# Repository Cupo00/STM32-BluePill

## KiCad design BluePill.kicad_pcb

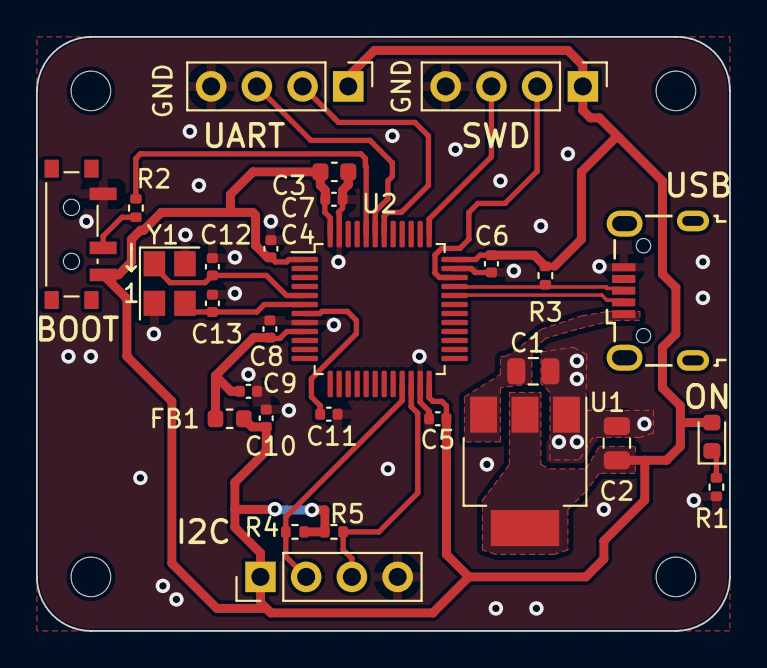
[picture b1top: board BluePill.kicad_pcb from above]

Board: 2 copper layers, 38.5 x 33.0 mm, 32 parts (0 on the bottom side), 18 nets.

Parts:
C1, C2: 22u; C_0805_2012Metric
C3: 10u; C_0603_1608Metric
C4, C5, C6, C7, C11: 100n; C_0402_1005Metric
C8: 10n; C_0402_1005Metric
C9, C10: 1u; C_0402_1005Metric
C12, C13: 10pF; C_0402_1005Metric
D1: LED; LED_0603_1608Metric
FB1: 120R; L_0603_1608Metric
H4, H4#2, H4#3, H4#4: MountingHole; MountingHole_2.2mm_M2
J1, J2, J3: Conn_01x04_Male; PinHeader_1x04_P2.54mm_Vertical
J4: USB_B_Micro; USB_Micro-B_Wuerth_629105150521
R1, R3, R4, R5: 1k5; R_0402_1005Metric
R2: 10k; R_0402_1005Metric
SW1: SW_SPDT; SW_SPDT_PCM12
U1: AMS1117-3.3; SOT-223-3_TabPin2
U2: STM32F103C8T6; LQFP-48_7x7mm_P0.5mm
Y1: 16MHz; Crystal_SMD_3225-4Pin_3.2x2.5mm

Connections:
+3.3V: C2.1, C3.1, C4.1, C5.1, C6.1, C7.2, C10.1, D1.2 (A), FB1.2, J1.1, J2.1, J3.1, R3.1, R4.1, R5.1, SW1.3 (C), U1.2 (VO), U2.1 (VBAT), U2.24 (VDD), U2.36 (VDD), U2.48 (VDD)
+3.3VA: C8.1, C9.1, FB1.1, U2.9 (VDDA)
/HSE_In: C12.1, U2.5 (PD0), Y1.1
/HSE_Out: C13.1, U2.6 (PD1), Y1.3
/I2C2_SCL: J2.2, R4.2, U2.21 (PB10)
/I2C2_SDA: J2.3, R5.2, U2.22 (PB11)
/NRST: C11.1, U2.7 (NRST)
/PWR_LED_K: D1.1 (K), R1.1
/SWCLCK: J3.3, U2.37 (PA14)
/SWDIO: J3.2, U2.34 (PA13)
/USART1_RX: J1.3, U2.43 (PB7)
/USART1_TX: J1.2, U2.42 (PB6)
/USB_D+: J4.3 (D+), R3.2, U2.33 (PA12)
/USB_D-: J4.2 (D-), U2.32 (PA11)
/sw_boot0: R2.1, SW1.2 (B)
GND: C1.2, C2.2, C3.2, C4.2, C5.2, C6.2, C7.1, C8.2, C9.2, C10.2, C11.2, C12.2, C13.2, J1.4, J2.4, J3.4, J4.5 (GND), R1.2, SW1.1 (A), U1.1 (GND), U2.8 (VSSA), U2.23 (VSS), U2.35 (VSS), U2.47 (VSS), Y1.2, Y1.4
unnamed: R2.2, U2.44 (BOOT0)
VBUS: C1.1, J4.1 (VBUS), U1.3 (VI)
